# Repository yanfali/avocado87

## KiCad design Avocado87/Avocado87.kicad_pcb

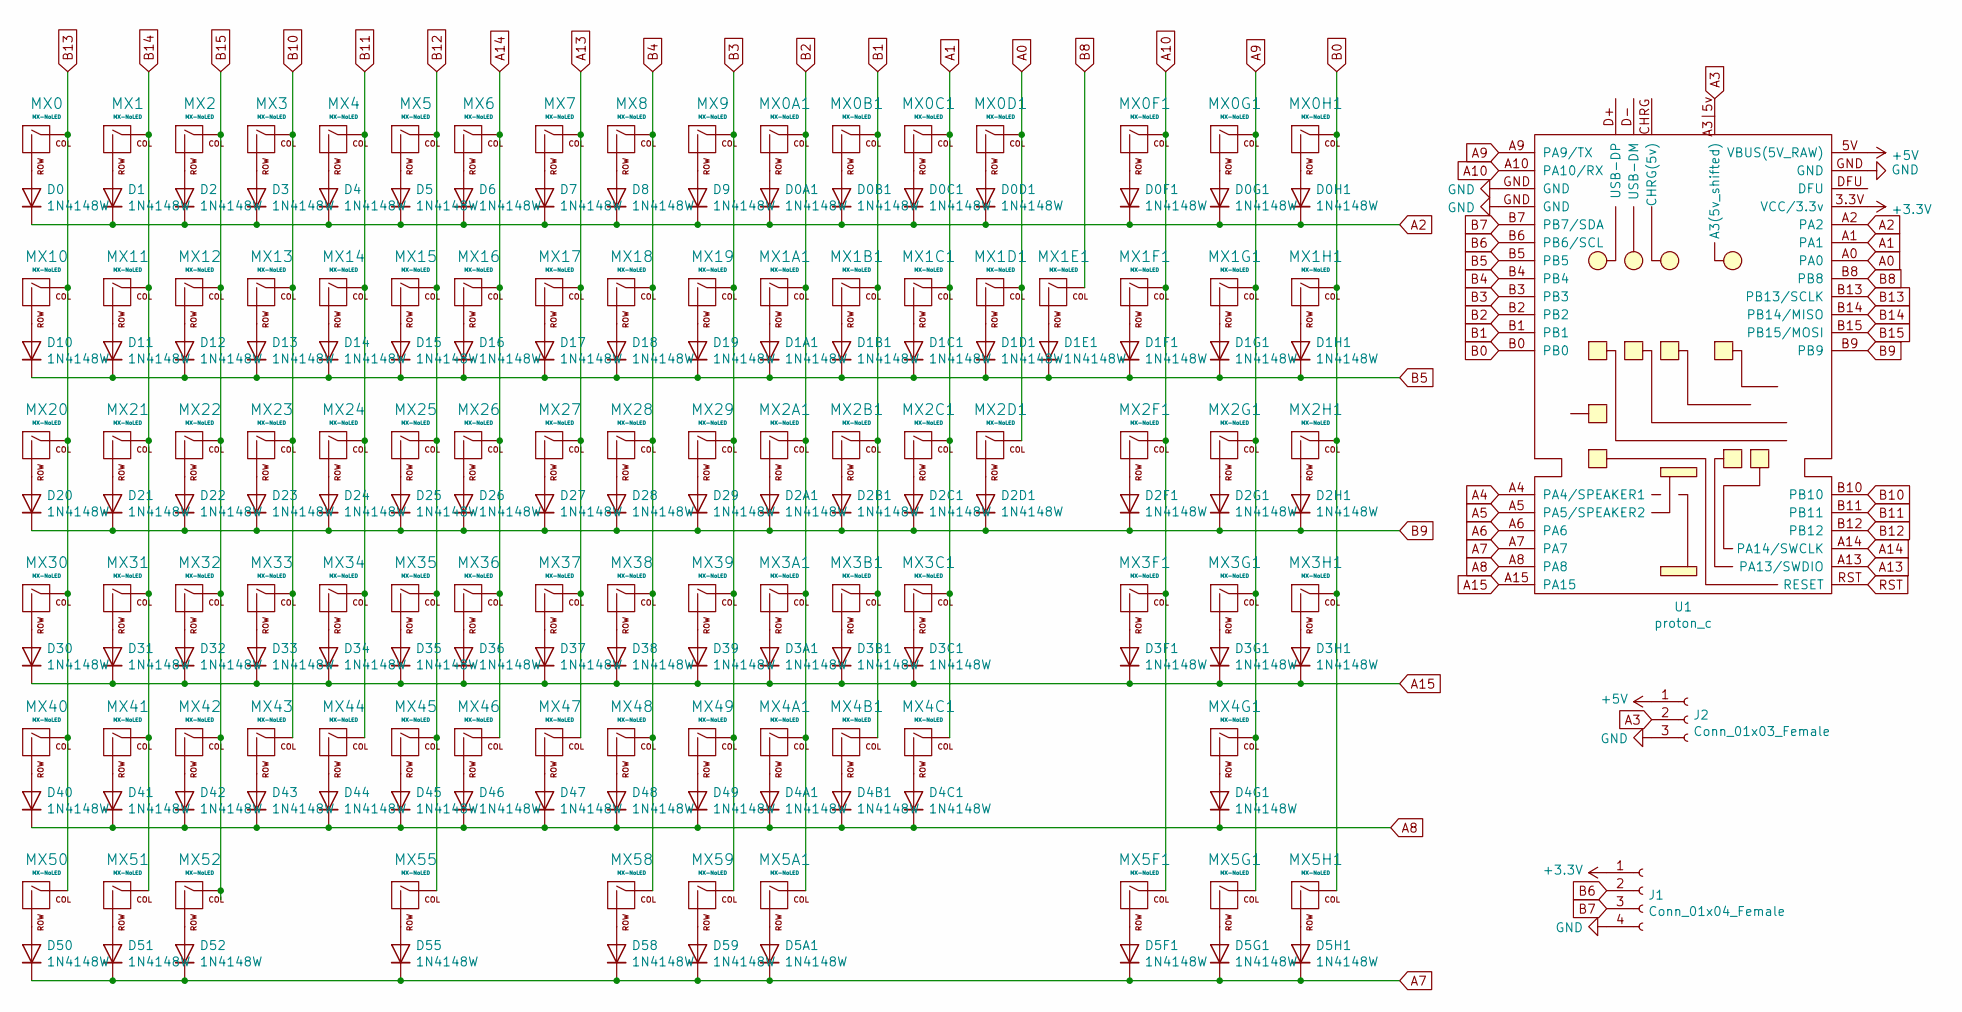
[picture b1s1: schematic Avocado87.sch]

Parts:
D0, D0A1, D0B1, D0C1, D0D1, D0F1, D0G1, D0H1, D1, D1A1, D1B1, D1C1, D1D1, D1E1, D1F1, D1G1, D1H1, D2, D2A1, D2B1, D2C1, D2D1, D2F1, D2G1, D2H1, D3, D3A1, D3B1, D3C1, D3F1, D3G1, D3H1, D4, D4A1, D4B1, D4C1, D4G1, D5, D5A1, D5F1, D5G1, D5H1, D6, D7, D8, D9, D10, D11, D12, D13, D14, D15, D16, D17, D18, D19, D20, D21, D22, D23, D24, D25, D26, D27, D28, D29, D30, D31, D32, D33, D34, D35, D36, D37, D38, D39, D40, D41, D42, D43, D44, D45, D46, D47, D48, D49, D50, D51, D52, D55, D58, D59: 1N4148W; D_SOD-123-Pretty
J1: Conn_01x04_Female; Fan_Pin_Header_Straight_1x04
J2: Conn_01x03_Female; PINHEAD1-3
MX0, MX0A1, MX0B1, MX0C1, MX0D1, MX0F1, MX0G1, MX0H1, MX1, MX1A1, MX1B1, MX1C1, MX1D1, MX1E1, MX1F1, MX1G1, MX1H1, MX2, MX2A1, MX2B1, MX2C1, MX2F1, MX2G1, MX2H1, MX3, MX3A1, MX3B1, MX3F1, MX3G1, MX3H1, MX4, MX4A1, MX4C1, MX4G1, MX5, MX5F1, MX5G1, MX5H1, MX6, MX7, MX8, MX9, MX10, MX11, MX12, MX13, MX14, MX15, MX16, MX17, MX18, MX19, MX21, MX22, MX23, MX24, MX25, MX26, MX27, MX28, MX29, MX31, MX32, MX33, MX34, MX35, MX36, MX37, MX38, MX39, MX41, MX42, MX43, MX44, MX45, MX46, MX47, MX48, MX49, MX51, MX59: MX-NoLED; MXOnly-1U-NoLED
MX2D1, MX5A1, MX20, MX50, MX52, MX58: MX-NoLED; MXOnly-1.5U-NoLED
MX3C1, MX40: MX-NoLED; MXOnly-2.25U-NoLED
MX4B1, MX30: MX-NoLED; MXOnly-1.75U-NoLED
MX55: MX-NoLED; MXOnly-7U-NoLED
U1: proton_c

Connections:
+3V3: J1.1, U1.3.3V (VCC/3.3v); also elsewhere on the board
+5V: J2.1, U1.5V (VBUS(5V_RAW)); also elsewhere on the board
A0: MX0D1.1 (COL), MX1D1.1 (COL), MX2D1.1 (COL), U1.A0
A1: MX0C1.1 (COL), MX1C1.1 (COL), MX2C1.1 (COL), MX3C1.1 (COL), MX4C1.1 (COL), U1.A1
A2: D0.1 (K), D0A1.1 (K), D0B1.1 (K), D0C1.1 (K), D0D1.1 (K), D0F1.1 (K), D0G1.1 (K), D0H1.1 (K), D1.1 (K), D2.1 (K), D3.1 (K), D4.1 (K), D5.1 (K), D6.1 (K), D7.1 (K), D8.1 (K), D9.1 (K), U1.A2
A3: J2.2, U1.A3|5v (A3(5v_shifted)); also elsewhere on the board
A7: D5A1.1 (K), D5F1.1 (K), D5G1.1 (K), D5H1.1 (K), D50.1 (K), D51.1 (K), D52.1 (K), D55.1 (K), D58.1 (K), D59.1 (K), U1.A7
A8: D4A1.1 (K), D4B1.1 (K), D4C1.1 (K), D4G1.1 (K), D40.1 (K), D41.1 (K), D42.1 (K), D43.1 (K), D44.1 (K), D45.1 (K), D46.1 (K), D47.1 (K), D48.1 (K), D49.1 (K), U1.A8
A9: MX0G1.1 (COL), MX1G1.1 (COL), MX2G1.1 (COL), MX3G1.1 (COL), MX4G1.1 (COL), MX5G1.1 (COL), U1.A9 (PA9/TX)
A10: MX0F1.1 (COL), MX1F1.1 (COL), MX2F1.1 (COL), MX3F1.1 (COL), MX5F1.1 (COL), U1.A10 (PA10/RX)
A13: MX7.1 (COL), MX17.1 (COL), MX27.1 (COL), MX37.1 (COL), MX47.1 (COL), U1.A13 (PA13/SWDIO)
A14: MX6.1 (COL), MX16.1 (COL), MX26.1 (COL), MX36.1 (COL), MX46.1 (COL), U1.A14 (PA14/SWCLK)
A15: D3A1.1 (K), D3B1.1 (K), D3C1.1 (K), D3F1.1 (K), D3G1.1 (K), D3H1.1 (K), D30.1 (K), D31.1 (K), D32.1 (K), D33.1 (K), D34.1 (K), D35.1 (K), D36.1 (K), D37.1 (K), D38.1 (K), D39.1 (K), U1.A15
B0: MX0H1.1 (COL), MX1H1.1 (COL), MX2H1.1 (COL), MX3H1.1 (COL), MX5H1.1 (COL), U1.B0
B1: MX0B1.1 (COL), MX1B1.1 (COL), MX2B1.1 (COL), MX3B1.1 (COL), MX4B1.1 (COL), U1.B1
B2: MX0A1.1 (COL), MX1A1.1 (COL), MX2A1.1 (COL), MX3A1.1 (COL), MX4A1.1 (COL), MX5A1.1 (COL), U1.B2
B3: MX9.1 (COL), MX19.1 (COL), MX29.1 (COL), MX39.1 (COL), MX49.1 (COL), MX59.1 (COL), U1.B3
B4: MX8.1 (COL), MX18.1 (COL), MX28.1 (COL), MX38.1 (COL), MX48.1 (COL), MX58.1 (COL), U1.B4
B5: D1A1.1 (K), D1B1.1 (K), D1C1.1 (K), D1D1.1 (K), D1E1.1 (K), D1F1.1 (K), D1G1.1 (K), D1H1.1 (K), D10.1 (K), D11.1 (K), D12.1 (K), D13.1 (K), D14.1 (K), D15.1 (K), D16.1 (K), D17.1 (K), D18.1 (K), D19.1 (K), U1.B5
B6: J1.2, U1.B6 (PB6/SCL); also elsewhere on the board
B7: J1.3, U1.B7 (PB7/SDA); also elsewhere on the board
B8: MX1E1.1 (COL), U1.B8
B9: D2A1.1 (K), D2B1.1 (K), D2C1.1 (K), D2D1.1 (K), D2F1.1 (K), D2G1.1 (K), D2H1.1 (K), D20.1 (K), D21.1 (K), D22.1 (K), D23.1 (K), D24.1 (K), D25.1 (K), D26.1 (K), D27.1 (K), D28.1 (K), D29.1 (K), U1.B9
B10: MX3.1 (COL), MX13.1 (COL), MX23.1 (COL), MX33.1 (COL), MX43.1 (COL), U1.B10
B11: MX4.1 (COL), MX14.1 (COL), MX24.1 (COL), MX34.1 (COL), MX44.1 (COL), U1.B11
B12: MX5.1 (COL), MX15.1 (COL), MX25.1 (COL), MX35.1 (COL), MX45.1 (COL), MX55.1 (COL), U1.B12
B13: MX0.1 (COL), MX10.1 (COL), MX20.1 (COL), MX30.1 (COL), MX40.1 (COL), MX50.1 (COL), U1.B13 (PB13/SCLK)
B14: MX1.1 (COL), MX11.1 (COL), MX21.1 (COL), MX31.1 (COL), MX41.1 (COL), MX51.1 (COL), U1.B14 (PB14/MISO)
B15: MX2.1 (COL), MX12.1 (COL), MX22.1 (COL), MX32.1 (COL), MX42.1 (COL), MX52.1 (COL), U1.B15 (PB15/MOSI)
GND: J1.4, J2.3, U1.GND; also elsewhere on the board
unnamed: D0.2 (A), MX0.2 (ROW)
unnamed: D0A1.2 (A), MX0A1.2 (ROW)
unnamed: D0B1.2 (A), MX0B1.2 (ROW)
unnamed: D0C1.2 (A), MX0C1.2 (ROW)
unnamed: D0D1.2 (A), MX0D1.2 (ROW)
unnamed: D0F1.2 (A), MX0F1.2 (ROW)
unnamed: D0G1.2 (A), MX0G1.2 (ROW)
unnamed: D0H1.2 (A), MX0H1.2 (ROW)
unnamed: D1.2 (A), MX1.2 (ROW)
unnamed: D1A1.2 (A), MX1A1.2 (ROW)
unnamed: D1B1.2 (A), MX1B1.2 (ROW)
unnamed: D1C1.2 (A), MX1C1.2 (ROW)
unnamed: D1D1.2 (A), MX1D1.2 (ROW)
unnamed: D1E1.2 (A), MX1E1.2 (ROW)
unnamed: D1F1.2 (A), MX1F1.2 (ROW)
unnamed: D1G1.2 (A), MX1G1.2 (ROW)
unnamed: D1H1.2 (A), MX1H1.2 (ROW)
unnamed: D2.2 (A), MX2.2 (ROW)
unnamed: D2A1.2 (A), MX2A1.2 (ROW)
unnamed: D2B1.2 (A), MX2B1.2 (ROW)
unnamed: D2C1.2 (A), MX2C1.2 (ROW)
unnamed: D2D1.2 (A), MX2D1.2 (ROW)
unnamed: D2F1.2 (A), MX2F1.2 (ROW)
unnamed: D2G1.2 (A), MX2G1.2 (ROW)
unnamed: D2H1.2 (A), MX2H1.2 (ROW)
unnamed: D3.2 (A), MX3.2 (ROW)
unnamed: D3A1.2 (A), MX3A1.2 (ROW)
unnamed: D3B1.2 (A), MX3B1.2 (ROW)
unnamed: D3C1.2 (A), MX3C1.2 (ROW)
unnamed: D3F1.2 (A), MX3F1.2 (ROW)
unnamed: D3G1.2 (A), MX3G1.2 (ROW)
unnamed: D3H1.2 (A), MX3H1.2 (ROW)
unnamed: D4.2 (A), MX4.2 (ROW)
unnamed: D4A1.2 (A), MX4A1.2 (ROW)
unnamed: D4B1.2 (A), MX4B1.2 (ROW)
unnamed: D4C1.2 (A), MX4C1.2 (ROW)
unnamed: D4G1.2 (A), MX4G1.2 (ROW)
unnamed: D5.2 (A), MX5.2 (ROW)
unnamed: D5A1.2 (A), MX5A1.2 (ROW)
unnamed: D5F1.2 (A), MX5F1.2 (ROW)
unnamed: D5G1.2 (A), MX5G1.2 (ROW)
unnamed: D5H1.2 (A), MX5H1.2 (ROW)
unnamed: D6.2 (A), MX6.2 (ROW)
unnamed: D7.2 (A), MX7.2 (ROW)
unnamed: D8.2 (A), MX8.2 (ROW)
unnamed: D9.2 (A), MX9.2 (ROW)
unnamed: D10.2 (A), MX10.2 (ROW)
unnamed: D11.2 (A), MX11.2 (ROW)
unnamed: D12.2 (A), MX12.2 (ROW)
unnamed: D13.2 (A), MX13.2 (ROW)
unnamed: D14.2 (A), MX14.2 (ROW)
unnamed: D15.2 (A), MX15.2 (ROW)
unnamed: D16.2 (A), MX16.2 (ROW)
unnamed: D17.2 (A), MX17.2 (ROW)
unnamed: D18.2 (A), MX18.2 (ROW)
unnamed: D19.2 (A), MX19.2 (ROW)
unnamed: D20.2 (A), MX20.2 (ROW)
unnamed: D21.2 (A), MX21.2 (ROW)
unnamed: D22.2 (A), MX22.2 (ROW)
unnamed: D23.2 (A), MX23.2 (ROW)
unnamed: D24.2 (A), MX24.2 (ROW)
unnamed: D25.2 (A), MX25.2 (ROW)
unnamed: D26.2 (A), MX26.2 (ROW)
unnamed: D27.2 (A), MX27.2 (ROW)
unnamed: D28.2 (A), MX28.2 (ROW)
unnamed: D29.2 (A), MX29.2 (ROW)
unnamed: D30.2 (A), MX30.2 (ROW)
unnamed: D31.2 (A), MX31.2 (ROW)
unnamed: D32.2 (A), MX32.2 (ROW)
unnamed: D33.2 (A), MX33.2 (ROW)
unnamed: D34.2 (A), MX34.2 (ROW)
unnamed: D35.2 (A), MX35.2 (ROW)
unnamed: D36.2 (A), MX36.2 (ROW)
unnamed: D37.2 (A), MX37.2 (ROW)
unnamed: D38.2 (A), MX38.2 (ROW)
unnamed: D39.2 (A), MX39.2 (ROW)
unnamed: D40.2 (A), MX40.2 (ROW)
unnamed: D41.2 (A), MX41.2 (ROW)
unnamed: D42.2 (A), MX42.2 (ROW)
unnamed: D43.2 (A), MX43.2 (ROW)
unnamed: D44.2 (A), MX44.2 (ROW)
unnamed: D45.2 (A), MX45.2 (ROW)
unnamed: D46.2 (A), MX46.2 (ROW)
unnamed: D47.2 (A), MX47.2 (ROW)
unnamed: D48.2 (A), MX48.2 (ROW)
unnamed: D49.2 (A), MX49.2 (ROW)
unnamed: D50.2 (A), MX50.2 (ROW)
unnamed: D51.2 (A), MX51.2 (ROW)
unnamed: D52.2 (A), MX52.2 (ROW)
unnamed: D55.2 (A), MX55.2 (ROW)
unnamed: D58.2 (A), MX58.2 (ROW)
unnamed: D59.2 (A), MX59.2 (ROW)

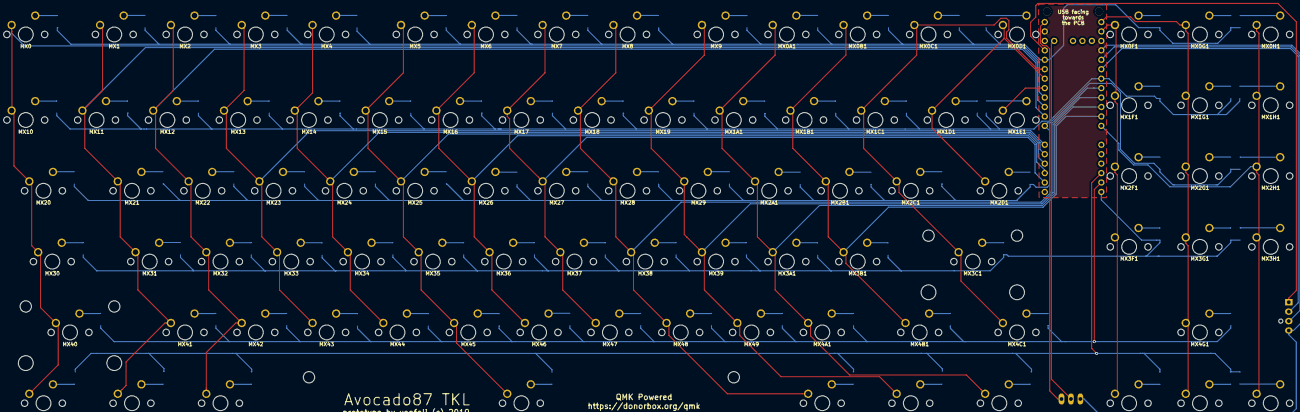
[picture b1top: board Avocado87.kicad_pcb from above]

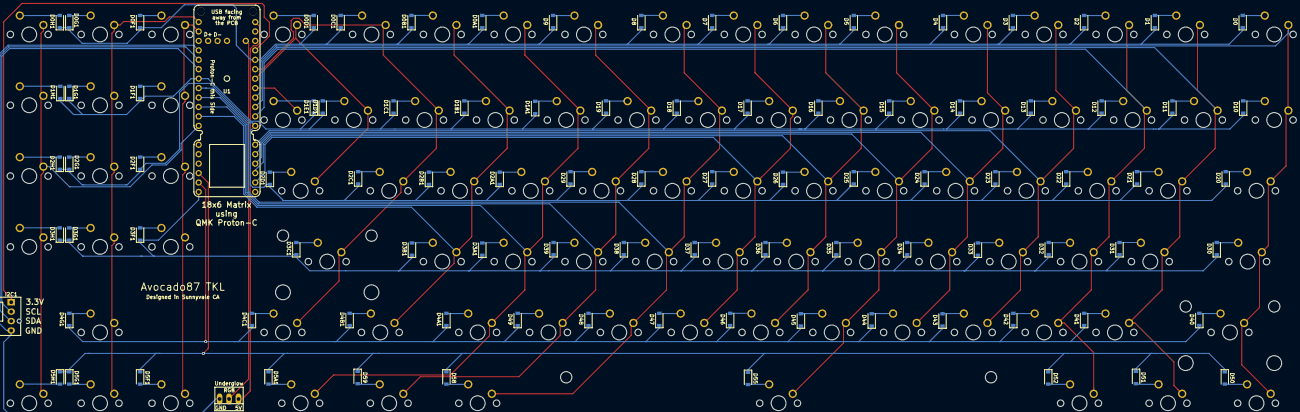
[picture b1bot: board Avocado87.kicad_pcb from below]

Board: 2 copper layers, 187 parts (95 on the bottom side), 122 nets.

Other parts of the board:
I2C1: Conn_01x04_Female; Fan_Pin_Header_Straight_1x04
Underglow: Conn_01x03_Female; PINHEAD1-3

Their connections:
+3V3: I2C1.1; also elsewhere on the board
+5V: Underglow.1; also elsewhere on the board
A3: Underglow.2; also elsewhere on the board
B6: I2C1.2; also elsewhere on the board
B7: I2C1.3; also elsewhere on the board
GND: I2C1.4, Underglow.3; also elsewhere on the board

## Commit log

2019-10-09 Add footprint libs
2019-10-09 Add proton-c
2019-10-09 Add footprints for switches
2019-10-09 Add footprint for proton-c
2019-10-09 Footprint work
    - sort out issues with naming and missing switches
    - remove unused symbols from proton-c
    - start labeling diodes correctly
2019-10-09 Placement and renames
2019-10-10 Routed PCB
2019-10-10 missing line
2019-10-10 Fine tuning
2019-10-10 Add a license
2019-10-10 Fix GND fill
2019-10-10 routing
2019-10-10 Add logos for CC NC
2019-10-11 Add i2c and underglow to pcb
2019-10-11 move underglow away from bottom of board
    Leave room for the strip
2019-10-11 Clean up stuff
2019-10-11 Add switch footprint ids
2019-10-11 USB pins

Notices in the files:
Avocado87/Avocado87.kicad_pcb:
prototype by yanfali (c) 2019
